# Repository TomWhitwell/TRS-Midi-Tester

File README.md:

# Music Thing Modular TRS Midi Tester

A simple passive tester to identify if you TRS Midi signal is [Type A or Type B](https://minimidi.world/). 

3 x boards from Oshpark cost about $2. 

When building, ensure you get your LEDs the right way round!  

BOM: 

1 x 3.5mm Stereo SMD Audio Jack CUI SJ-3524-SMT-TR or equivalent  
1 x 330 Ohm 0603 resistor   
2 x 1206 LEDs suitable for reverse mounting KPTL-3216SYCK or similar (A 1206 LED with a circular / cylindrical lens - not a square lens - will fit into the hole.)

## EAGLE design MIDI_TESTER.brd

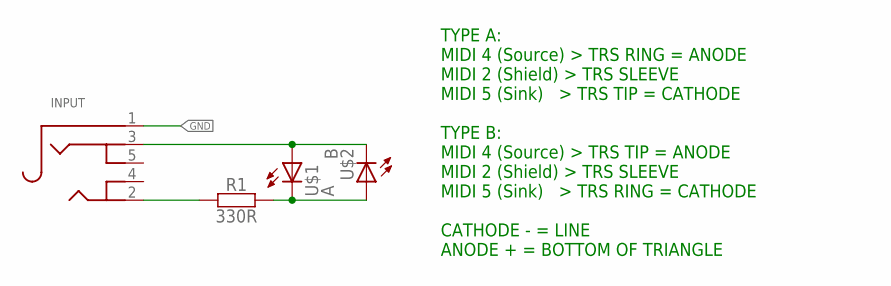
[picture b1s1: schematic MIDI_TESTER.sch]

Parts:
INPUT: AUDIO_3.5MMJACK; 4UCONN_19269
R1: 330R; C0603
U$1: A; LED-1206-REVERSE-PLATED
U$2: B; LED-1206-REVERSE-PLATED

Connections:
GND: INPUT.1
unnamed: INPUT.2, R1.1
unnamed: INPUT.3, U$1.A, U$2.C
unnamed: R1.2, U$1.C, U$2.A

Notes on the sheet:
TYPE A: MIDI 4 (Source) > TRS RING = ANODE MIDI 2 (Shield) > TRS SLEEVE MIDI 5 (Sink) > TRS TIP = CATHODE TYPE B: MIDI 4 (Source) > TRS TIP = ANODE MIDI 2 (Shield) > TRS SLEEVE MIDI 5 (Sink) > TRS RING = CATHODE CATHODE - = LINE ANODE + = BOTTOM OF TRIANGLE

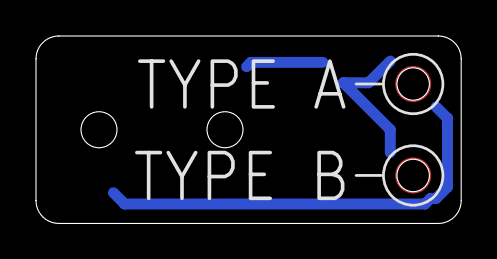
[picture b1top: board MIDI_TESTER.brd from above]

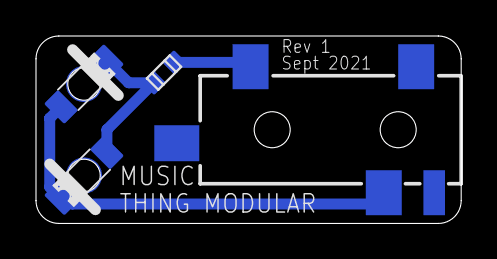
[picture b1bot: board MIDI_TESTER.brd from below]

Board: 2 copper layers, 23.6 x 10.4 mm, 4 parts (2 on the bottom side), 3 nets.

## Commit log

2021-09-16 Initial design sent to fab
2022-06-03 images

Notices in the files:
parts and their libraries:
microbuilder: This work is placed in the public domain, and may be freely used for commercial and non-commercial work with the following conditions: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
